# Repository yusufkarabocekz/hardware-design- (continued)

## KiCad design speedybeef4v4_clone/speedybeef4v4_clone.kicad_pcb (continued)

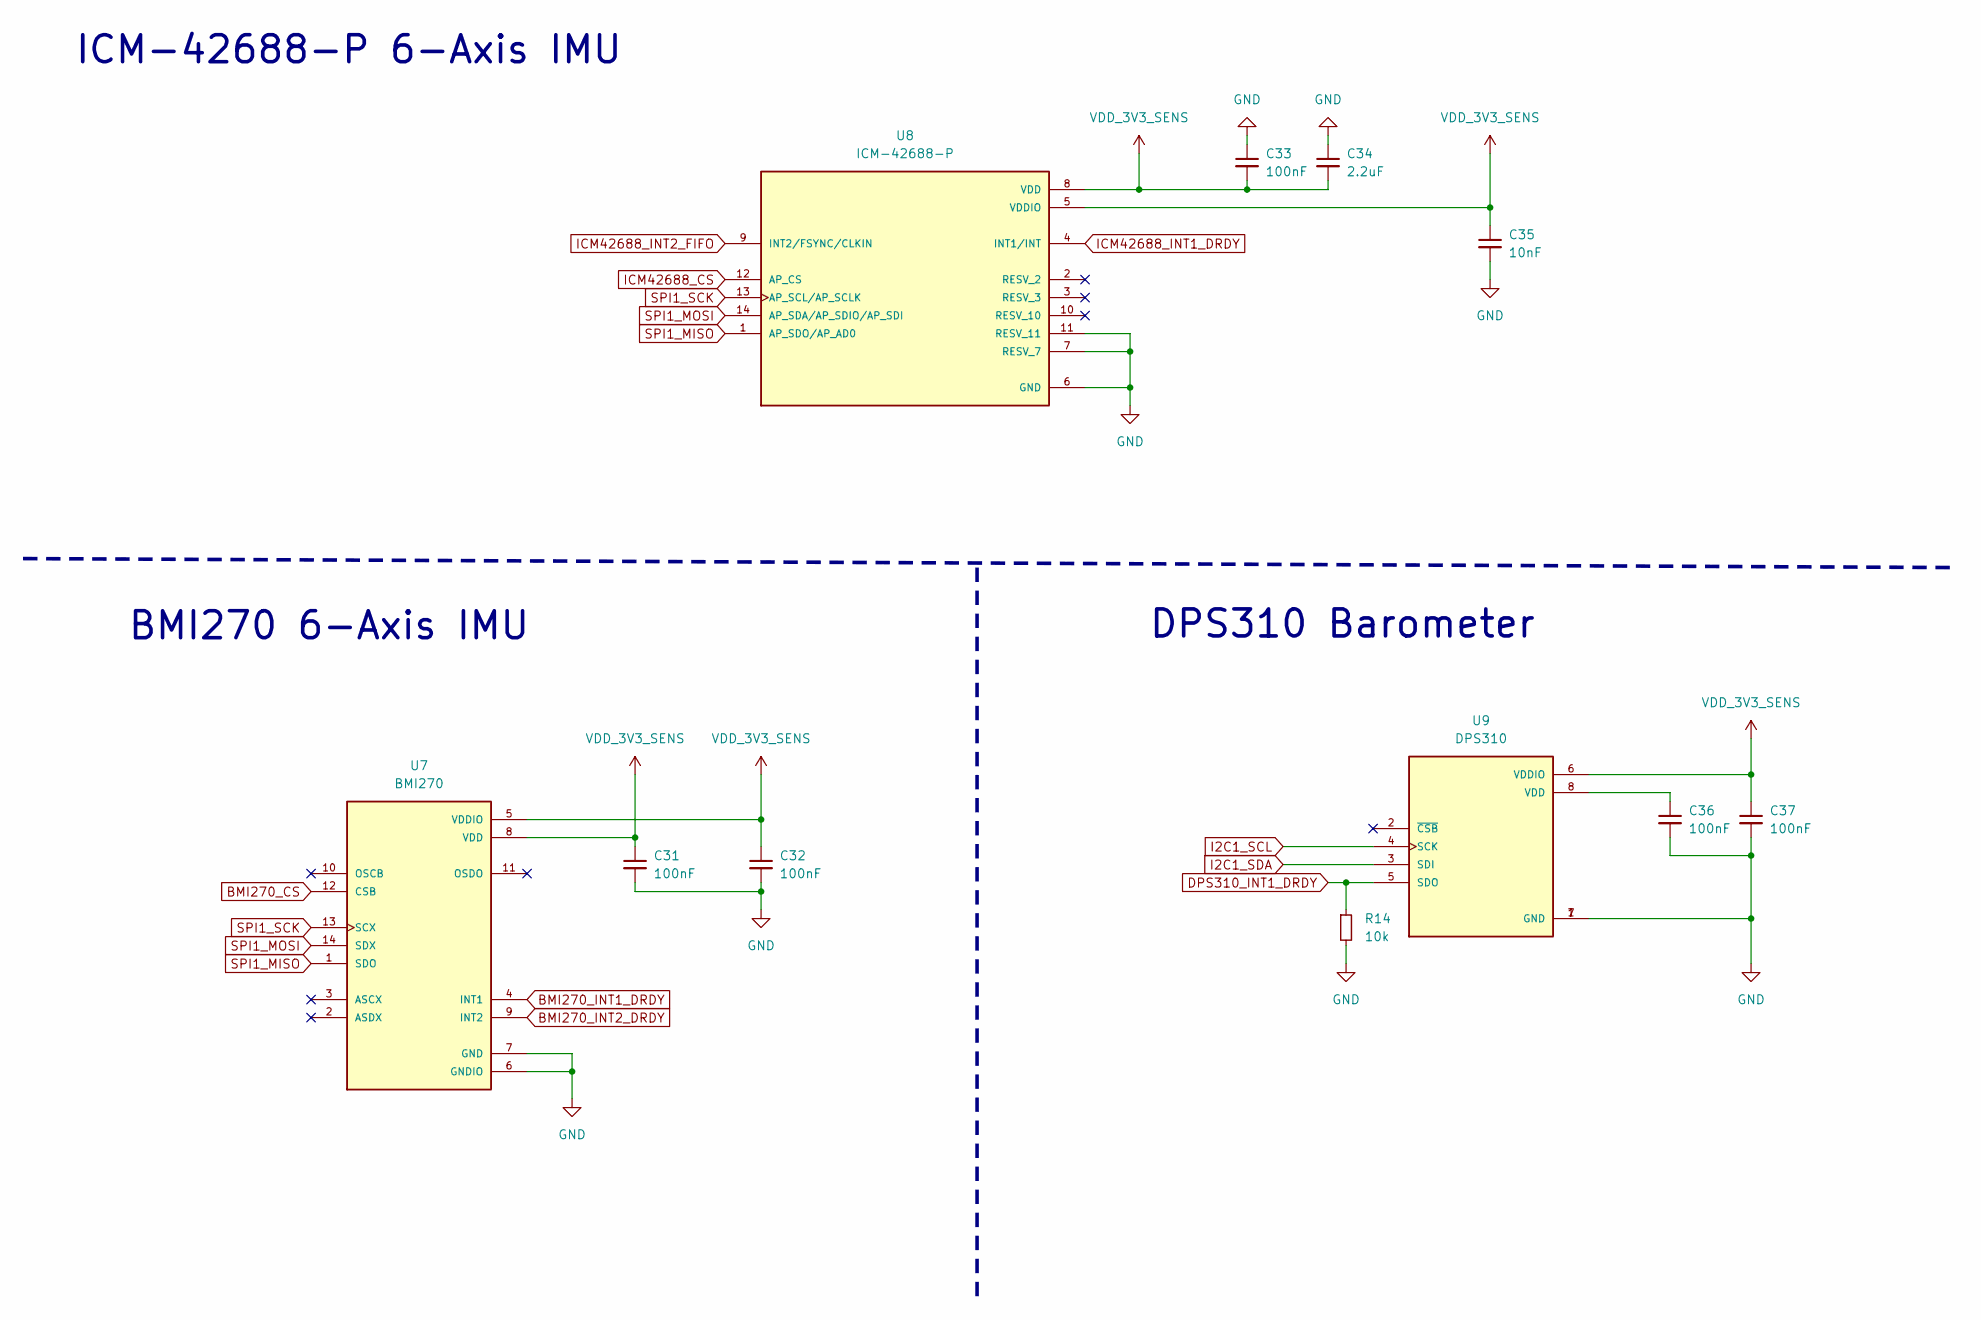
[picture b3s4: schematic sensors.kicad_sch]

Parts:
C31, C32, C33, C36, C37: 100nF; C_0402_1005Metric
C34: 2.2uF; C_0402_1005Metric
C35: 10nF; C_0402_1005Metric
R14: 10k; R_0402_1005Metric
U7: BMI270; XDCR_BMI270
U8: ICM-42688-P; PQFN50P300X250X97-14N; PARTREV 1.2
U9: DPS310; XDCR_DPS310

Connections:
BMI270_CS: U7.12 (CSB); also elsewhere on the board
BMI270_INT1_DRDY: U7.4 (INT1); also elsewhere on the board
BMI270_INT2_DRDY: U7.9 (INT2); also elsewhere on the board
DPS310_INT1_DRDY: R14.1, U9.5 (SDO); also elsewhere on the board
GND: C31.2, C32.2, C33.1, C34.1, C35.2, C36.2, C37.2, R14.2, U7.6 (GNDIO), U7.7 (GND), U8.6 (GND), U8.7 (RESV_7), U8.11 (RESV_11), U9.1 (GND), U9.7 (GND); also elsewhere on the board
I2C1_SCL: U9.4 (SCK); also elsewhere on the board
I2C1_SDA: U9.3 (SDI); also elsewhere on the board
ICM42688_CS: U8.12 (AP_CS); also elsewhere on the board
ICM42688_INT1_DRDY: U8.4 (INT1/INT); also elsewhere on the board
ICM42688_INT2_FIFO: U8.9 (INT2/FSYNC/CLKIN); also elsewhere on the board
unnamed: C36.1, U9.8 (VDD)
SPI1_MISO: U7.1 (SDO), U8.1 (AP_SDO/AP_AD0); also elsewhere on the board
SPI1_MOSI: U7.14 (SDX), U8.14 (AP_SDA/AP_SDIO/AP_SDI); also elsewhere on the board
SPI1_SCK: U7.13 (SCX), U8.13 (AP_SCL/AP_SCLK); also elsewhere on the board
VDD_3V3_SENS: C31.1, C32.1, C33.2, C34.2, C35.1, C37.1, U7.5 (VDDIO), U7.8 (VDD), U8.5 (VDDIO), U8.8 (VDD), U9.6 (VDDIO); also elsewhere on the board

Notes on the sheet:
DPS310 Barometer
ICM-42688-P 6-Axis IMU
BMI270 6-Axis IMU

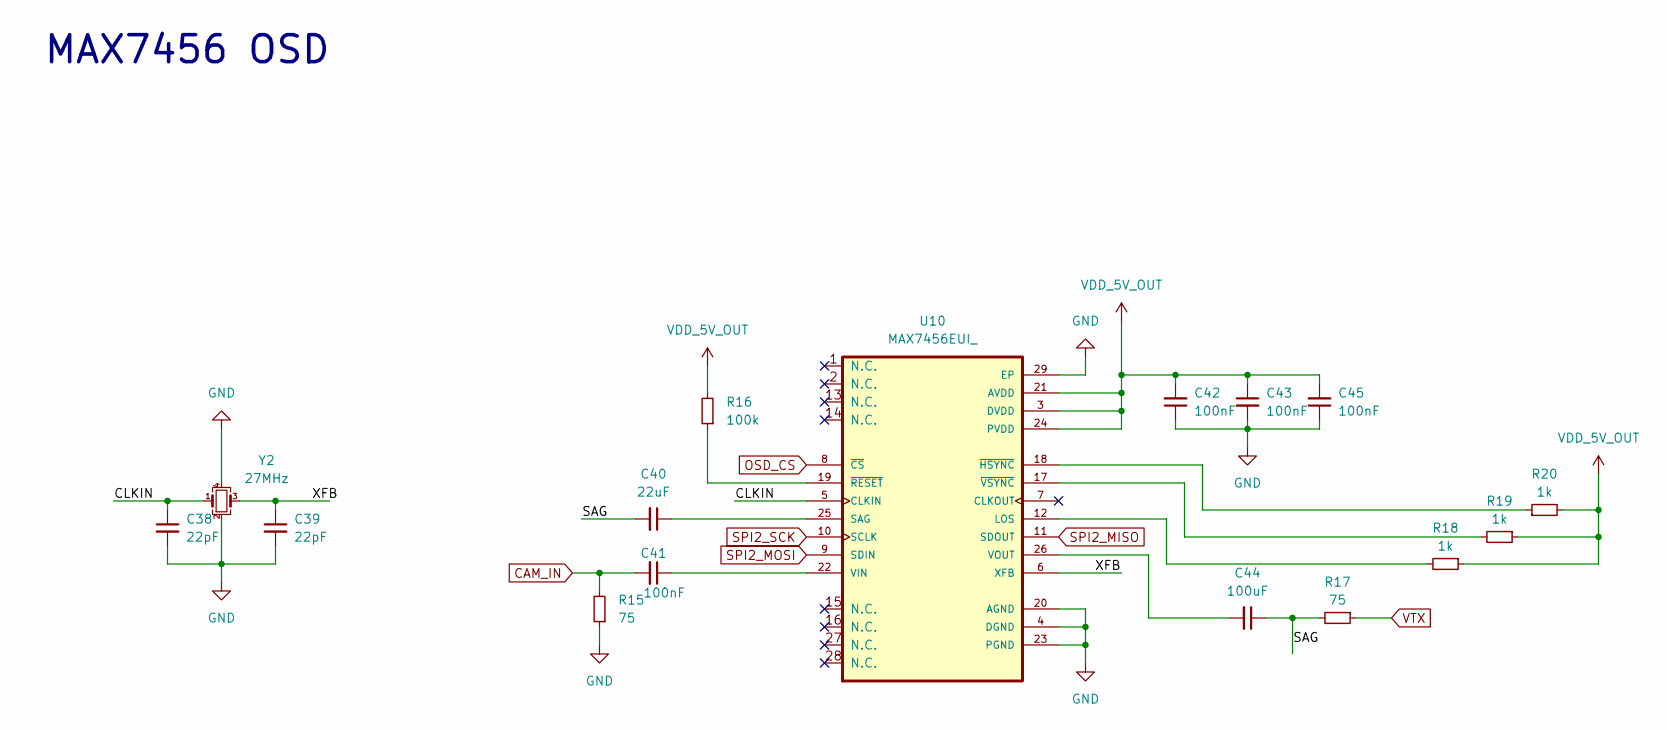
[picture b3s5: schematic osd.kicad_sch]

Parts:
C38, C39: 22pF; C_0402_1005Metric
C40: 22uF; C_0805_2012Metric
C41, C42, C43, C45: 100nF; C_0402_1005Metric
C44: 100uF; C_1210_3225Metric
R15, R17: 75; R_0402_1005Metric
R16: 100k; R_0402_1005Metric
R18, R19, R20: 1k; R_0402_1005Metric
U10: MAX7456EUI_; SOP65P637X110-28N
Y2: 27MHz; Crystal_SMD_SeikoEpson_FA238V-4Pin_3.2x2.5mm

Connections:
/OSD/CLKIN: C38.1, U10.5 (CLKIN), Y2.1
/OSD/SAG: C40.2, C44.1, R17.2
/OSD/XFB: C39.1, U10.6 (XFB), Y2.3
CAM_IN: C41.2, R15.2; also elsewhere on the board
GND: C38.2, C39.2, C42.1, C43.2, C45.1, R15.1, U10.4 (DGND), U10.20 (AGND), U10.23 (PGND), U10.29 (EP), Y2.2, Y2.4; also elsewhere on the board
unnamed: R18.2, U10.12 (LOS)
unnamed: C40.1, U10.25 (SAG)
unnamed: C41.1, U10.22 (VIN)
unnamed: C44.2, U10.26 (VOUT)
unnamed: R20.1, U10.18 (~HSYNC)
unnamed: R16.1, U10.19 (~RESET)
unnamed: R19.2, U10.17 (~VSYNC)
OSD_CS: U10.8 (~CS); also elsewhere on the board
SPI2_MISO: U10.11 (SDOUT); also elsewhere on the board
SPI2_MOSI: U10.9 (SDIN); also elsewhere on the board
SPI2_SCK: U10.10 (SCLK); also elsewhere on the board
VDD_5V_OUT: C42.2, C43.1, C45.2, R16.2, R18.1, R19.1, R20.2, U10.3 (DVDD), U10.21 (AVDD), U10.24 (PVDD); also elsewhere on the board
VTX: R17.1

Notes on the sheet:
MAX7456 OSD

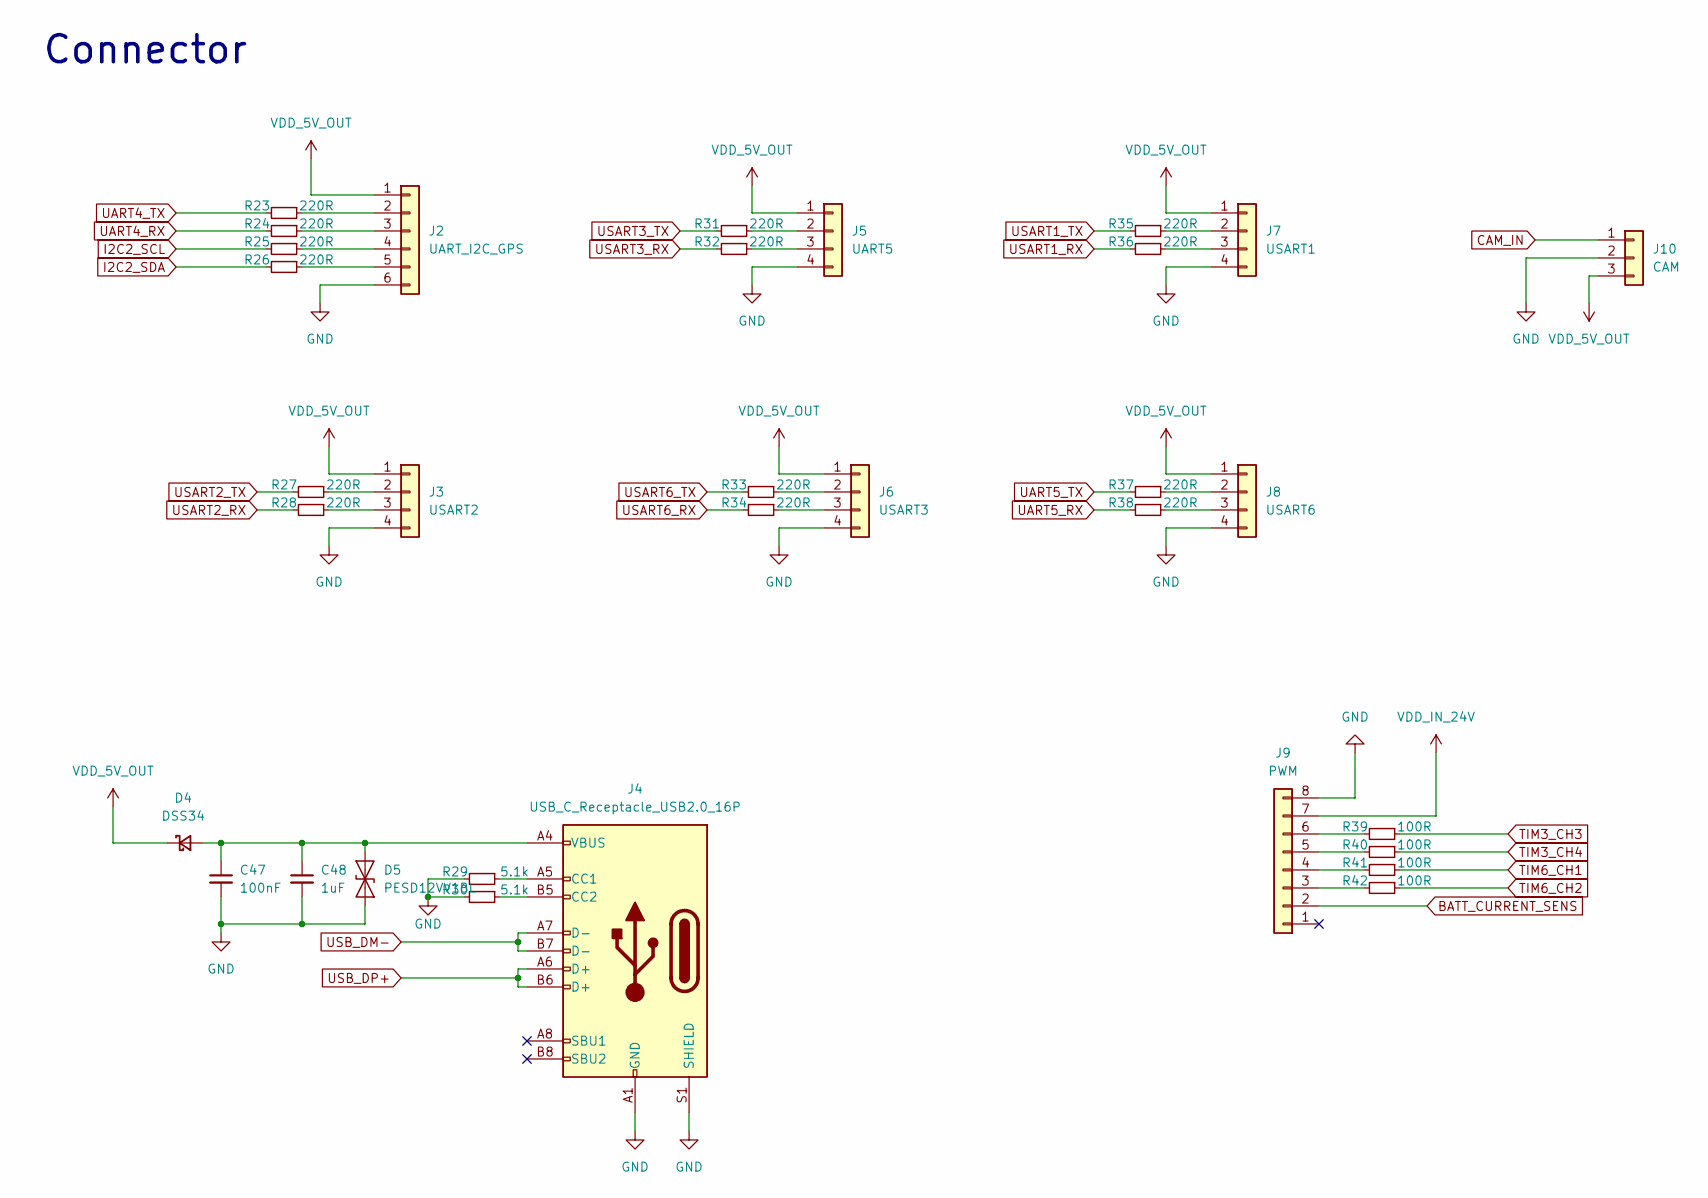
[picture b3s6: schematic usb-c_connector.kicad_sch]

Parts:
C47: 100nF; C_0402_1005Metric
C48: 1uF; C_0402_1005Metric
D4: DSS34; Nexperia_CFP3_SOD-123W
D5: PESD12VV1BL; D_SOD-882
J2: UART_I2C_GPS; JST_GH_SM06B-GHS-TB_1x06-1MP_P1.25mm_Horizontal
J3: USART2; JST_GH_SM04B-GHS-TB_1x04-1MP_P1.25mm_Horizontal
J4: USB_C_Receptacle_USB2.0_16P; USB_C_Receptacle_GCT_USB4110
J5: UART5; JST_GH_SM04B-GHS-TB_1x04-1MP_P1.25mm_Horizontal
J6: USART3; JST_GH_SM04B-GHS-TB_1x04-1MP_P1.25mm_Horizontal
J7: USART1; JST_GH_SM04B-GHS-TB_1x04-1MP_P1.25mm_Horizontal
J8: USART6; JST_GH_SM04B-GHS-TB_1x04-1MP_P1.25mm_Horizontal
J9: PWM; JST_GH_SM08B-GHS-TB_1x08-1MP_P1.25mm_Horizontal
J10: CAM; JST_GH_SM03B-GHS-TB_1x03-1MP_P1.25mm_Horizontal
R23, R24, R25, R26, R27, R28, R31, R32, R33, R34, R35, R36, R37, R38: 220R; R_0402_1005Metric
R29, R30: 5.1k; R_0402_1005Metric
R39, R40, R41, R42: 100R; R_0402_1005Metric

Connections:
BATT_CURRENT_SENS: J9.2; also elsewhere on the board
CAM_IN: J10.1; also elsewhere on the board
GND: C47.2, C48.2, D5.1 (A1), J2.6, J3.4, J4.A1 (GND), J4.A12 (GND), J4.B1 (GND), J4.B12 (GND), J4.S1 (SHIELD), J5.4, J6.4, J7.4, J8.4, J9.8, J10.2, R29.2, R30.2; also elsewhere on the board
I2C2_SCL: R25.2; also elsewhere on the board
I2C2_SDA: R26.2; also elsewhere on the board
unnamed: C47.1, C48.1, D4.2 (A), D5.2 (A2), J4.A4 (VBUS), J4.A9 (VBUS), J4.B4 (VBUS), J4.B9 (VBUS)
unnamed: J2.2, R23.1
unnamed: J2.3, R24.1
unnamed: J2.4, R25.1
unnamed: J2.5, R26.1
unnamed: J3.2, R27.1
unnamed: J3.3, R28.1
unnamed: J4.A5 (CC1), R29.1
unnamed: J4.B5 (CC2), R30.1
unnamed: J5.2, R31.1
unnamed: J5.3, R32.1
unnamed: J6.2, R33.1
unnamed: J6.3, R34.1
unnamed: J7.2, R35.1
unnamed: J7.3, R36.1
unnamed: J8.2, R37.1
unnamed: J8.3, R38.1
unnamed: J9.3, R42.2
unnamed: J9.4, R41.2
unnamed: J9.5, R40.2
unnamed: J9.6, R39.2
TIM3_CH3: R39.1; also elsewhere on the board
TIM3_CH4: R40.1; also elsewhere on the board
TIM6_CH1: R41.1; also elsewhere on the board
TIM6_CH2: R42.1; also elsewhere on the board
UART4_RX: R24.2; also elsewhere on the board
UART4_TX: R23.2; also elsewhere on the board
UART5_RX: R38.2; also elsewhere on the board
UART5_TX: R37.2; also elsewhere on the board
USART3_RX: R32.2; also elsewhere on the board
USART3_TX: R31.2; also elsewhere on the board
USB_DM-: J4.A7 (D-), J4.B7 (D-); also elsewhere on the board
USB_DP+: J4.A6 (D+), J4.B6 (D+); also elsewhere on the board
VDD_5V_OUT: D4.1 (K), J2.1, J3.1, J5.1, J6.1, J7.1, J8.1, J10.3; also elsewhere on the board
VDD_IN_24V: J9.7; also elsewhere on the board

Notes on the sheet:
Connector

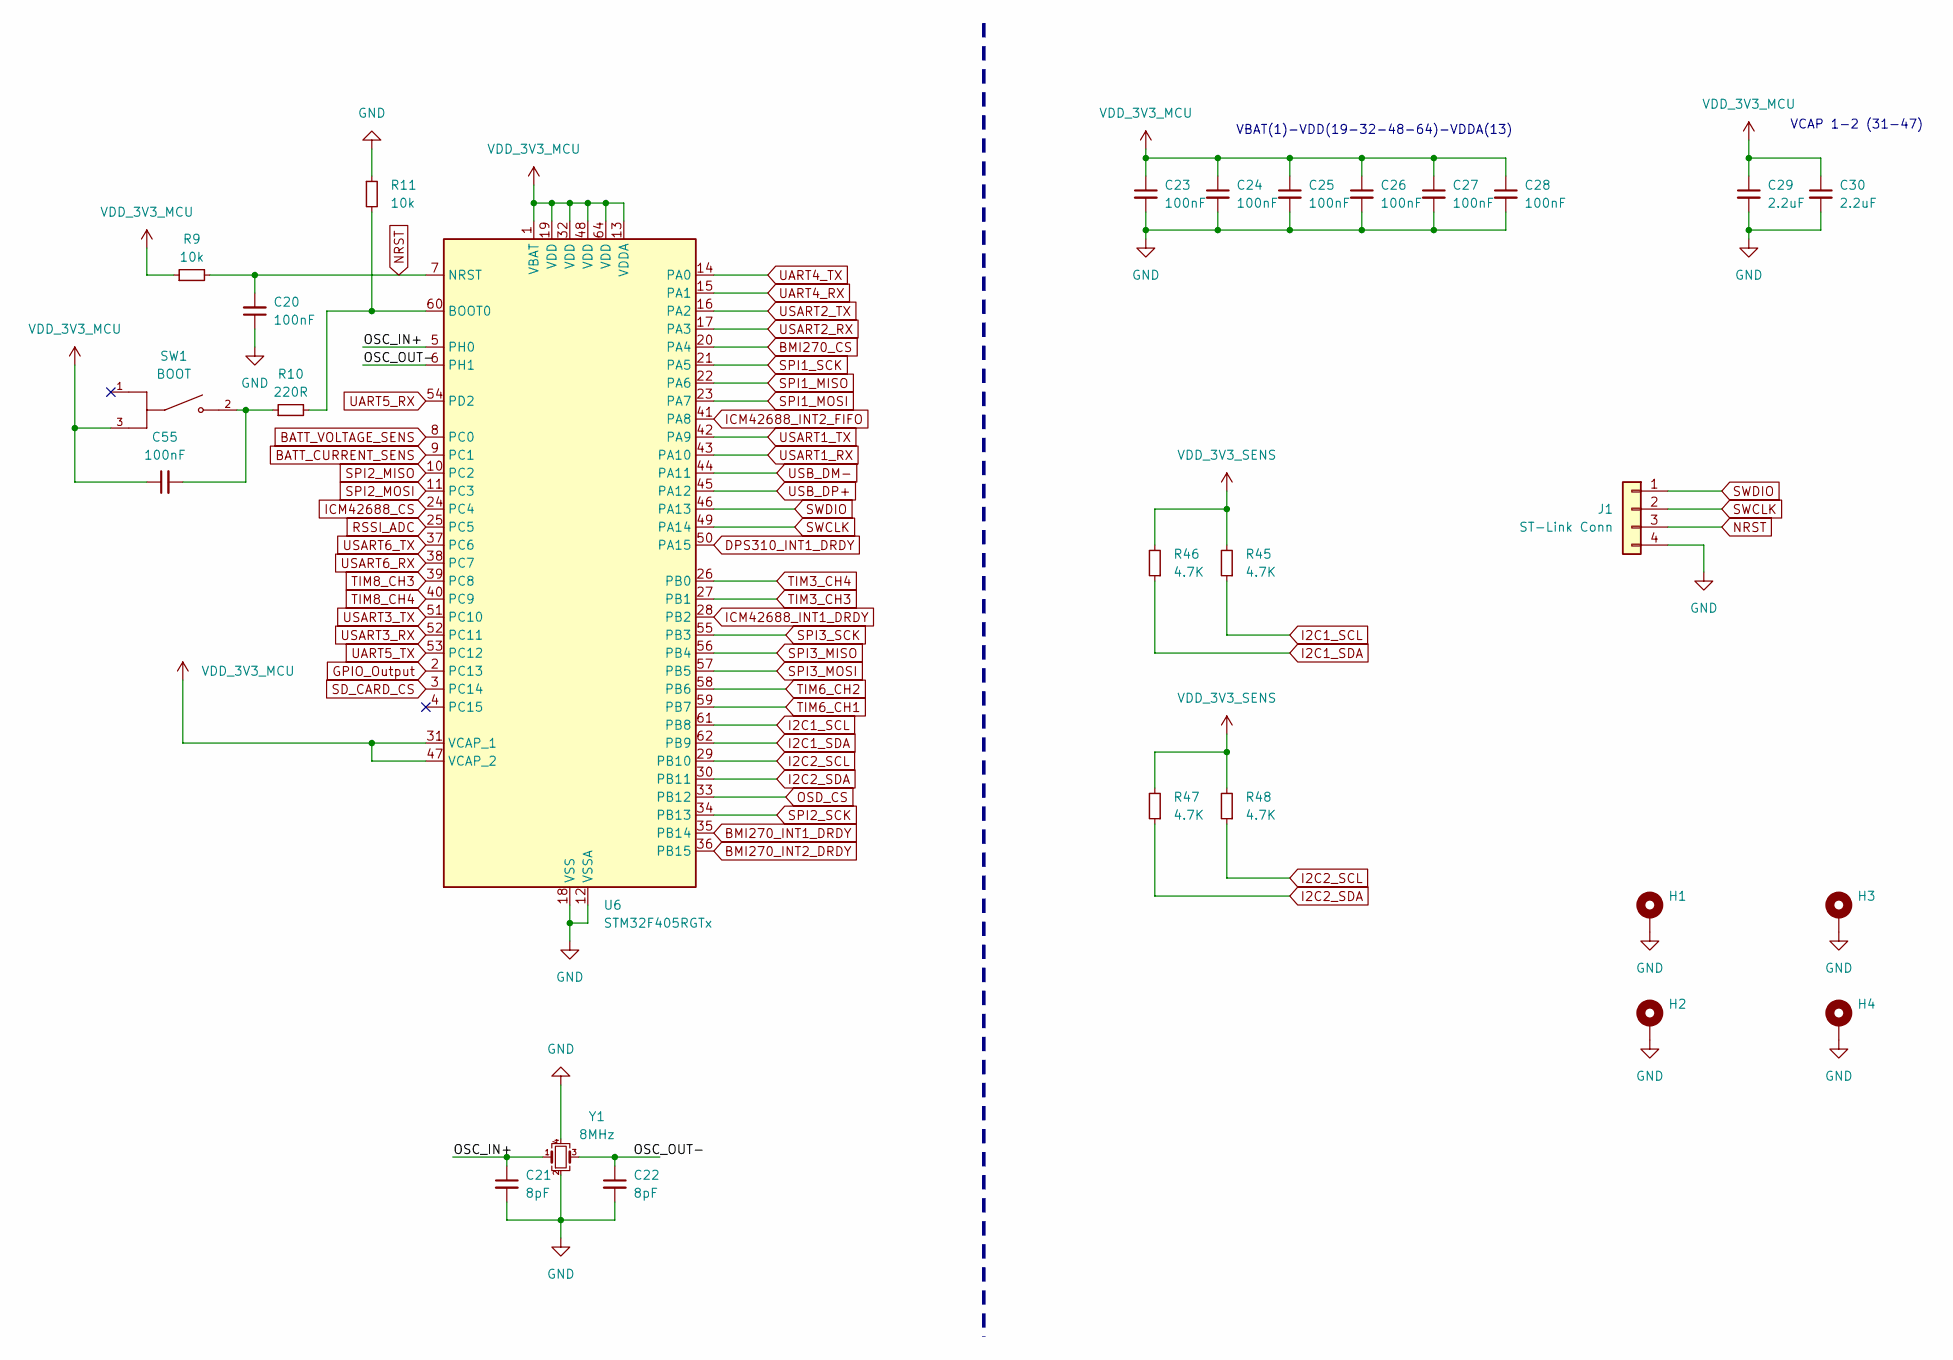
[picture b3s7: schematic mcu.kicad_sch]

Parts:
C20, C23, C24, C25, C26, C27, C28, C55: 100nF; C_0402_1005Metric
C21, C22: 8pF; C_0402_1005Metric
C29, C30: 2.2uF; C_0402_1005Metric
H1, H2, H3, H4: MountingHole_Pad; MountingHole_3.2mm_M3_Pad_Via
J1: ST-Link Conn; JST_GH_SM04B-GHS-TB_1x04-1MP_P1.25mm_Horizontal
R9, R11: 10k; R_0402_1005Metric
R10: 220R; R_0402_1005Metric
R45, R46, R47, R48: 4.7K; R_0402_1005Metric
SW1: BOOT; SW_TL3340AF160QG; PARTREV B
U6: STM32F405RGTx; LQFP-64_10x10mm_P0.5mm
Y1: 8MHz; Crystal_SMD_SeikoEpson_FA238V-4Pin_3.2x2.5mm

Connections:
/MCU/OSC_IN+: C21.1, U6.5 (PH0), Y1.1
/MCU/OSC_OUT-: C22.1, U6.6 (PH1), Y1.3
BATT_CURRENT_SENS: U6.9 (PC1); also elsewhere on the board
BATT_VOLTAGE_SENS: U6.8 (PC0); also elsewhere on the board
BMI270_CS: U6.20 (PA4); also elsewhere on the board
BMI270_INT1_DRDY: U6.35 (PB14); also elsewhere on the board
BMI270_INT2_DRDY: U6.36 (PB15); also elsewhere on the board
DPS310_INT1_DRDY: U6.50 (PA15); also elsewhere on the board
GND: C20.1, C21.2, C22.2, C23.2, C24.2, C25.2, C26.2, C27.2, C28.2, C29.2, C30.2, H1.1, H2.1, H3.1, H4.1, J1.4, R11.1, U6.12 (VSSA), U6.18 (VSS), U6.63 (VSS), Y1.2, Y1.4; also elsewhere on the board
GPIO_Output: U6.2 (PC13)
I2C1_SCL: R45.1, U6.61 (PB8); also elsewhere on the board
I2C1_SDA: R46.1, U6.62 (PB9); also elsewhere on the board
I2C2_SCL: R48.1, U6.29 (PB10); also elsewhere on the board
I2C2_SDA: R47.1, U6.30 (PB11); also elsewhere on the board
ICM42688_CS: U6.24 (PC4); also elsewhere on the board
ICM42688_INT1_DRDY: U6.28 (PB2); also elsewhere on the board
ICM42688_INT2_FIFO: U6.41 (PA8); also elsewhere on the board
NRST: C20.2, J1.3, R9.2, U6.7 (NRST)
unnamed: C55.2, R10.1, SW1.2
unnamed: R10.2, R11.2, U6.60 (BOOT0)
OSD_CS: U6.33 (PB12); also elsewhere on the board
RSSI_ADC: U6.25 (PC5)
SD_CARD_CS: U6.3 (PC14); also elsewhere on the board
SPI1_MISO: U6.22 (PA6); also elsewhere on the board
SPI1_MOSI: U6.23 (PA7); also elsewhere on the board
SPI1_SCK: U6.21 (PA5); also elsewhere on the board
SPI2_MISO: U6.10 (PC2); also elsewhere on the board
SPI2_MOSI: U6.11 (PC3); also elsewhere on the board
SPI2_SCK: U6.34 (PB13); also elsewhere on the board
SPI3_MISO: U6.56 (PB4); also elsewhere on the board
SPI3_MOSI: U6.57 (PB5); also elsewhere on the board
SPI3_SCK: U6.55 (PB3); also elsewhere on the board
SWCLK: J1.2, U6.49 (PA14)
SWDIO: J1.1, U6.46 (PA13)
TIM3_CH3: U6.27 (PB1); also elsewhere on the board
TIM3_CH4: U6.26 (PB0); also elsewhere on the board
TIM6_CH1: U6.59 (PB7); also elsewhere on the board
TIM6_CH2: U6.58 (PB6); also elsewhere on the board
TIM8_CH3: U6.39 (PC8)
TIM8_CH4: U6.40 (PC9)
UART4_RX: U6.15 (PA1); also elsewhere on the board
UART4_TX: U6.14 (PA0); also elsewhere on the board
UART5_RX: U6.54 (PD2); also elsewhere on the board
UART5_TX: U6.53 (PC12); also elsewhere on the board
USART1_RX: U6.43 (PA10)
USART1_TX: U6.42 (PA9)
USART2_RX: U6.17 (PA3)
USART2_TX: U6.16 (PA2)
USART3_RX: U6.52 (PC11); also elsewhere on the board
USART3_TX: U6.51 (PC10); also elsewhere on the board
USART6_RX: U6.38 (PC7)
USART6_TX: U6.37 (PC6)
USB_DM-: U6.44 (PA11); also elsewhere on the board
USB_DP+: U6.45 (PA12); also elsewhere on the board
VDD_3V3_MCU: C23.1, C24.1, C25.1, C26.1, C27.1, C28.1, C29.1, C30.1, C55.1, R9.1, SW1.3, U6.1 (VBAT), U6.13 (VDDA), U6.19 (VDD), U6.31 (VCAP_1), U6.32 (VDD), U6.47 (VCAP_2), U6.48 (VDD), U6.64 (VDD); also elsewhere on the board
VDD_3V3_SENS: R45.2, R46.2, R47.2, R48.2; also elsewhere on the board

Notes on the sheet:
VBAT(1)-VDD(19-32-48-64)-VDDA(13)
VCAP 1-2 (31-47)

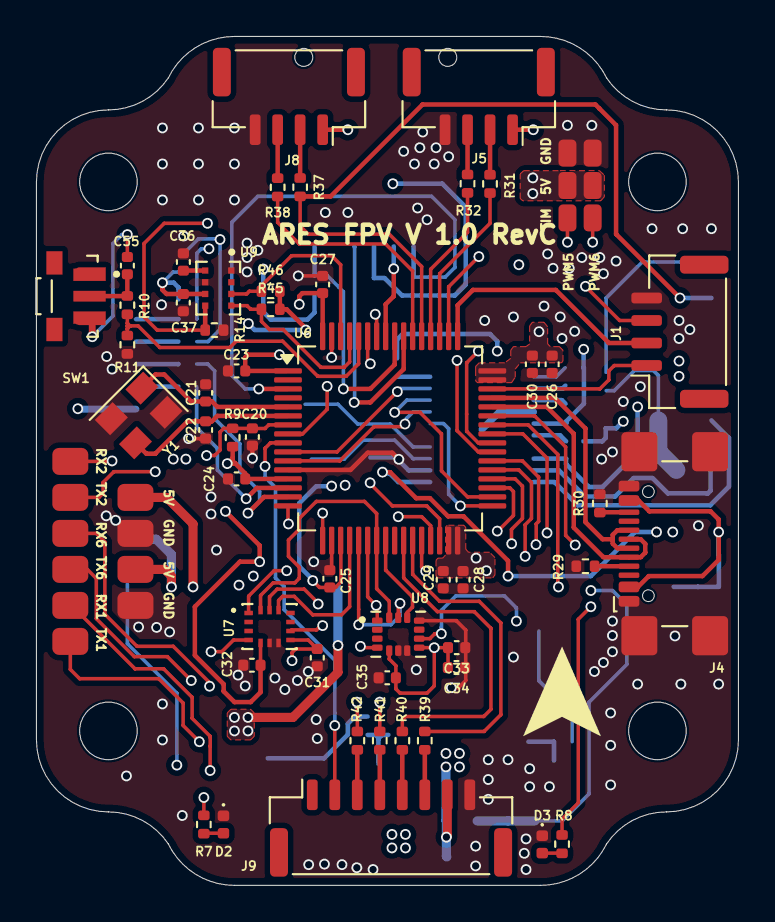
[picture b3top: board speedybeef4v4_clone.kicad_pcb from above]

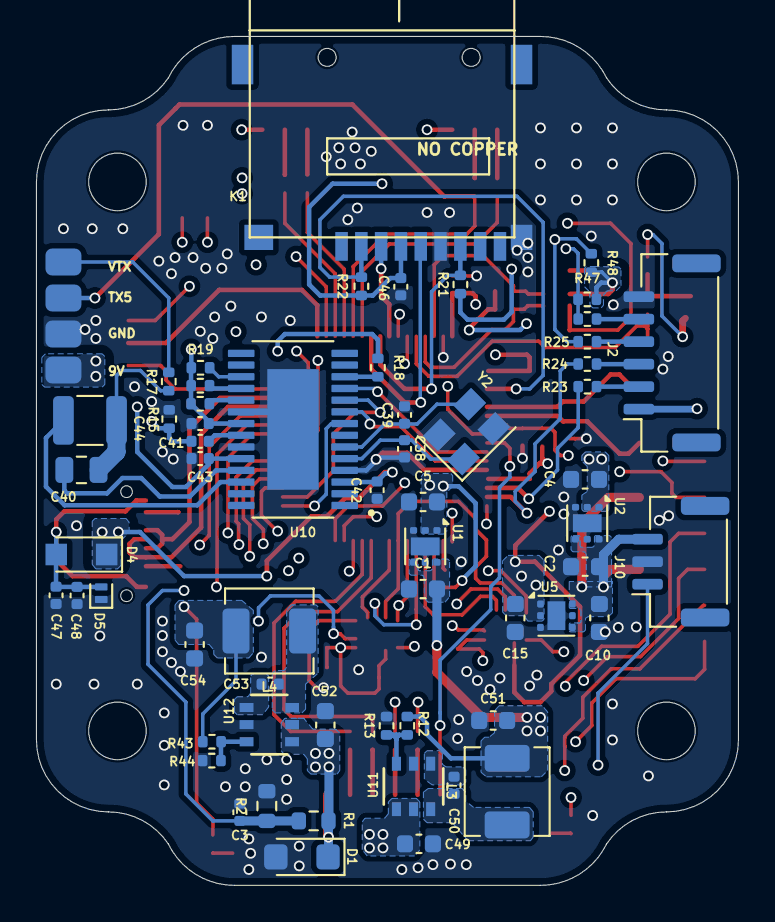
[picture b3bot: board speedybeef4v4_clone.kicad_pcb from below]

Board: 6 copper layers, 39.0 x 47.2 mm, 113 parts (59 on the bottom side), 85 nets.

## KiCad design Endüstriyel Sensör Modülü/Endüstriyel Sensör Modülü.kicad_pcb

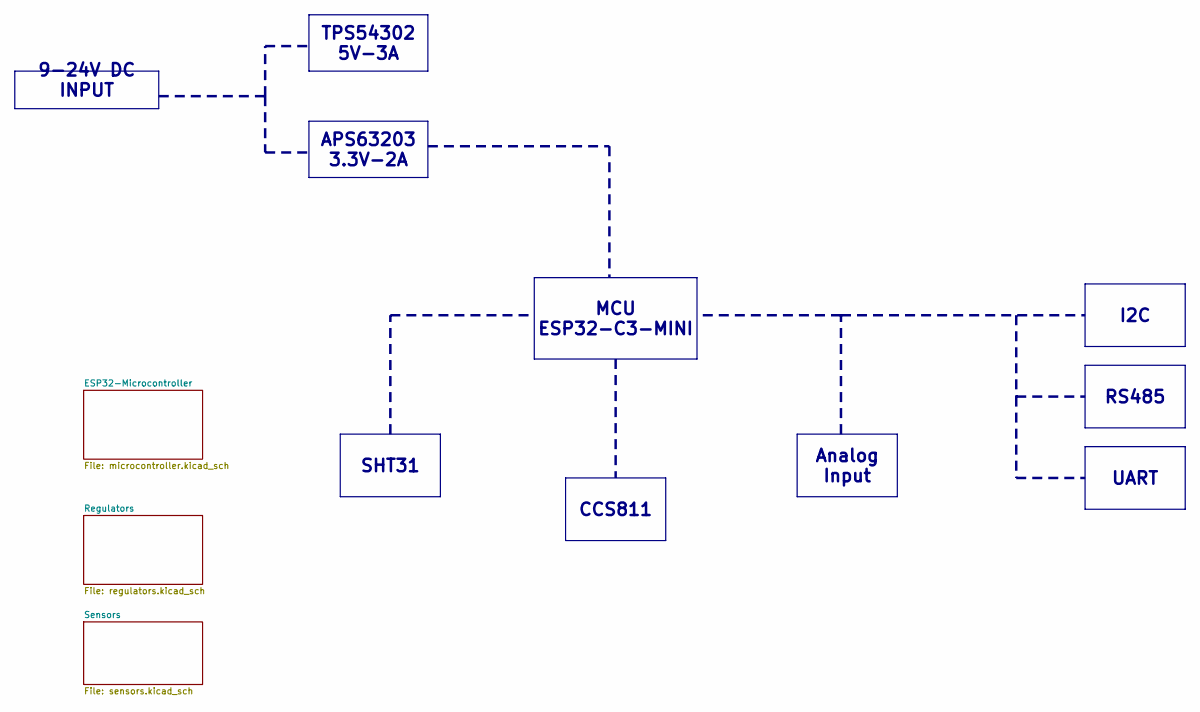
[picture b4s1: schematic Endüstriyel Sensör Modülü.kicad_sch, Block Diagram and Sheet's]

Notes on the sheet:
SHT31
MCU ESP32-C3-MINI
CCS811
APS63203 3.3V-2A
I2C
Analog Input
UART
9-24V DC INPUT
TPS54302 5V-3A
RS485

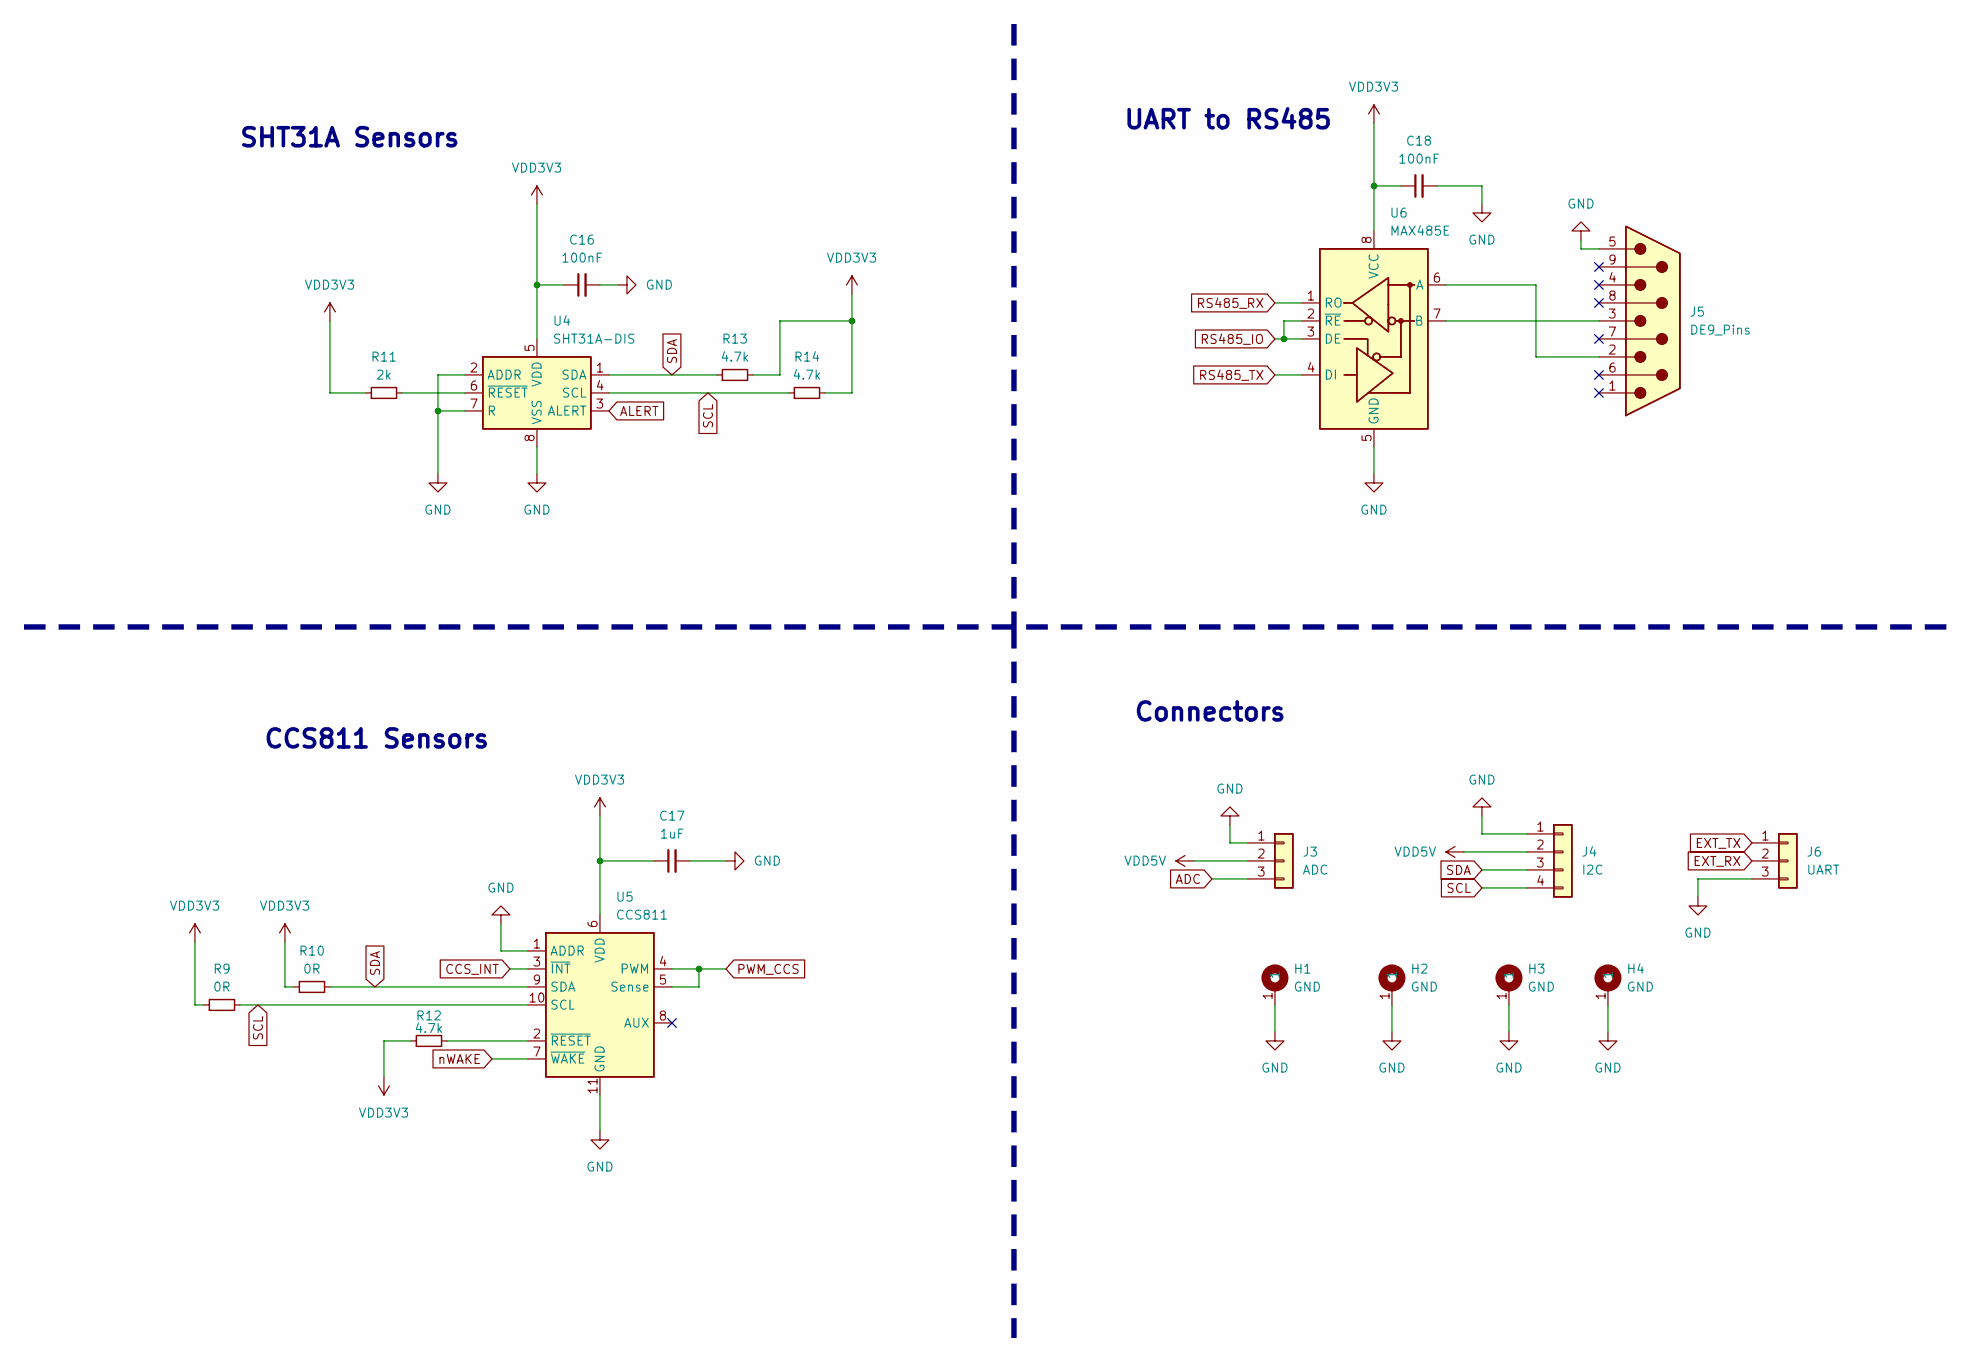
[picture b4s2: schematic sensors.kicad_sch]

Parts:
C16, C18: 100nF; C_0603_1608Metric
C17: 1uF; C_0603_1608Metric
H1, H2, H3, H4: GND; MountingHole_3.2mm_M3_ISO7380_Pad_TopBottom
J3: ADC; FanPinHeader_1x03_P2.54mm_Vertical
J4: I2C; FanPinHeader_1x04_P2.54mm_Vertical
J5: DE9_Pins; DSUB-9_Pins_Horizontal_P2.77x2.84mm_EdgePinOffset4.94mm_Hou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
J6: UART; FanPinHeader_1x03_P2.54mm_Vertical
R9, R10: 0R; R_0603_1608Metric
R11: 2k; R_0603_1608Metric
R12, R13, R14: 4.7k; R_0603_1608Metric
U4: SHT31A-DIS; DFN-8-1EP_2x2mm_P0.5mm_EP0.6x1.2mm
U5: CCS811; AMS_LGA-10-1EP_2.7x4mm_P0.6mm
U6: MAX485E; SOIC-8_3.9x4.9mm_P1.27mm

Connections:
ADC: J3.3; also elsewhere on the board
ALERT: U4.3 (ALERT); also elsewhere on the board
CCS_INT: U5.3 (~INT); also elsewhere on the board
EXT_RX: J6.2; also elsewhere on the board
EXT_TX: J6.1; also elsewhere on the board
GND: C16.2, C17.2, C18.2, H1.1, H2.1, H3.1, H4.1, J3.1, J4.1, J5.5, J6.3, U4.2 (ADDR), U4.7 (R), U4.8 (VSS), U4.9 (VSS), U5.1 (ADDR), U5.11 (GND), U6.5 (GND); also elsewhere on the board
unnamed: R11.2, U4.6 (~RESET)
unnamed: R12.2, U5.2 (~RESET)
unnamed: J5.2, U6.6 (A)
unnamed: J5.3, U6.7 (B)
PWM_CCS: U5.4 (PWM), U5.5 (Sense); also elsewhere on the board
RS485_IO: U6.2 (~RE), U6.3 (DE); also elsewhere on the board
RS485_RX: U6.1 (RO); also elsewhere on the board
RS485_TX: U6.4 (DI); also elsewhere on the board
SCL: J4.4, R9.2, R14.1, U4.4 (SCL), U5.10 (SCL); also elsewhere on the board
SDA: J4.3, R10.2, R13.1, U4.1 (SDA), U5.9 (SDA); also elsewhere on the board
VDD3V3: C16.1, C17.1, C18.1, R9.1, R10.1, R11.1, R12.1, R13.2, R14.2, U4.5 (VDD), U5.6 (VDD), U6.8 (VCC); also elsewhere on the board
VDD5V: J3.2, J4.2; also elsewhere on the board
nWAKE: U5.7 (~WAKE); also elsewhere on the board

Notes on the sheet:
UART to RS485
CCS811 Sensors
Connectors
SHT31A Sensors

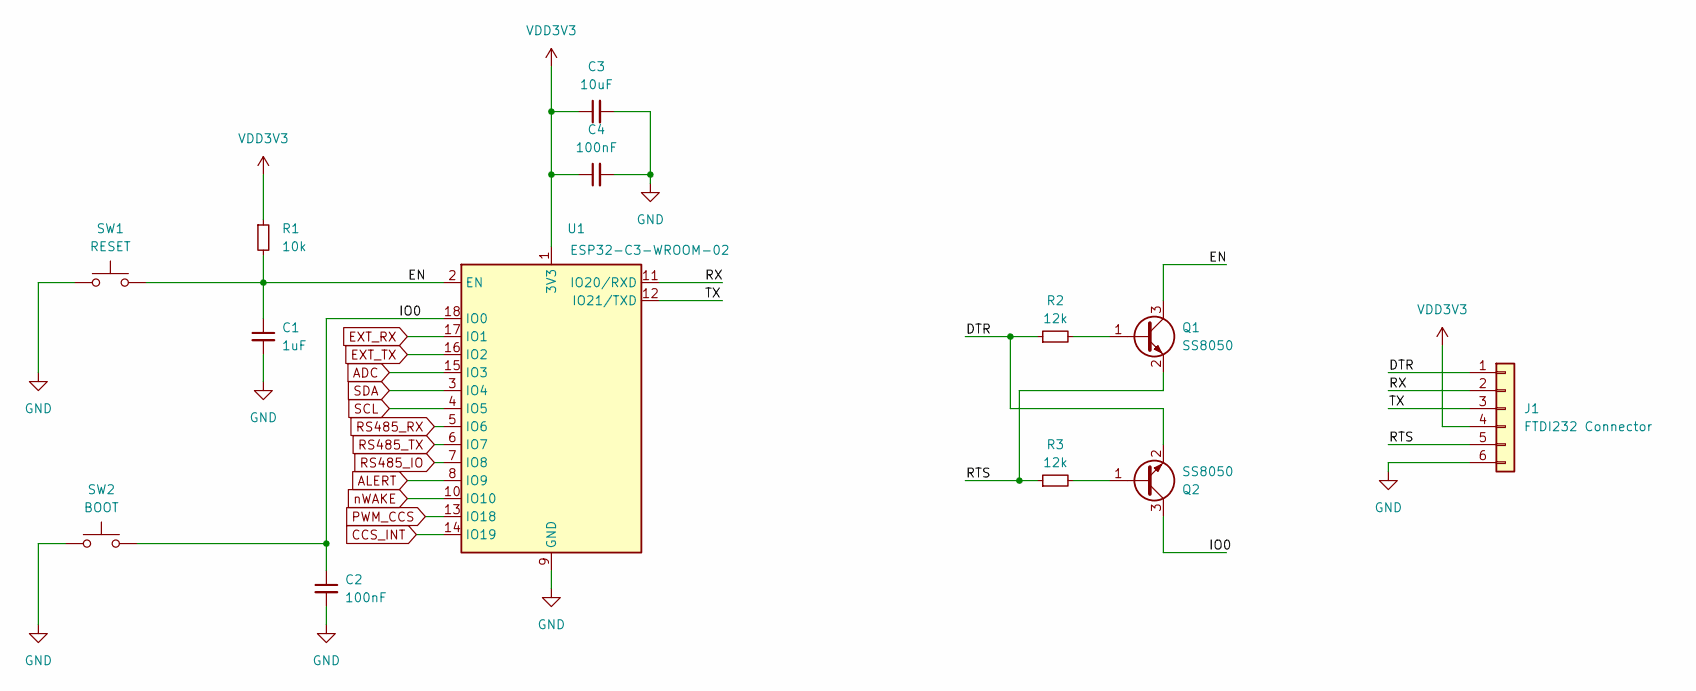
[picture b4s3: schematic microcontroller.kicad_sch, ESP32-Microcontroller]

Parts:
C1: 1uF; C_0603_1608Metric
C2, C4: 100nF; C_0603_1608Metric
C3: 10uF; C_0603_1608Metric
J1: FTDI232 Connector; PinHeader_1x06_P2.54mm_Horizontal
Q1, Q2: SS8050; SOT-23
R1: 10k; R_0603_1608Metric
R2, R3: 12k; R_0603_1608Metric
SW1: RESET; SW_Tactile_SPST_NO_Straight_CK_PTS636Sx25SMTRLFS
SW2: BOOT; SW_Tactile_SPST_NO_Straight_CK_PTS636Sx25SMTRLFS
U1: ESP32-C3-WROOM-02

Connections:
/ESP32-Microcontroller/DTR: J1.1, Q2.2 (E), R2.1
/ESP32-Microcontroller/EN: C1.1, Q1.3 (C), R1.2, SW1.2, U1.2 (EN)
/ESP32-Microcontroller/IO0: C2.1, Q2.3 (C), SW2.2, U1.18 (IO0)
/ESP32-Microcontroller/RTS: J1.5, Q1.2 (E), R3.1
/ESP32-Microcontroller/RX: J1.2, U1.11 (IO20/RXD)
/ESP32-Microcontroller/TX: J1.3, U1.12 (IO21/TXD)
ADC: U1.15 (IO3); also elsewhere on the board
ALERT: U1.8 (IO9); also elsewhere on the board
CCS_INT: U1.14 (IO19); also elsewhere on the board
EXT_RX: U1.17 (IO1); also elsewhere on the board
EXT_TX: U1.16 (IO2); also elsewhere on the board
GND: C1.2, C2.2, C3.2, C4.2, J1.6, SW1.1, SW2.1, U1.9 (GND), U1.19 (GND); also elsewhere on the board
unnamed: Q1.1 (B), R2.2
unnamed: Q2.1 (B), R3.2
PWM_CCS: U1.13 (IO18); also elsewhere on the board
RS485_IO: U1.7 (IO8); also elsewhere on the board
RS485_RX: U1.5 (IO6); also elsewhere on the board
RS485_TX: U1.6 (IO7); also elsewhere on the board
SCL: U1.4 (IO5); also elsewhere on the board
SDA: U1.3 (IO4); also elsewhere on the board
VDD3V3: C3.1, C4.1, J1.4, R1.1, U1.1 (3V3); also elsewhere on the board
nWAKE: U1.10 (IO10); also elsewhere on the board
